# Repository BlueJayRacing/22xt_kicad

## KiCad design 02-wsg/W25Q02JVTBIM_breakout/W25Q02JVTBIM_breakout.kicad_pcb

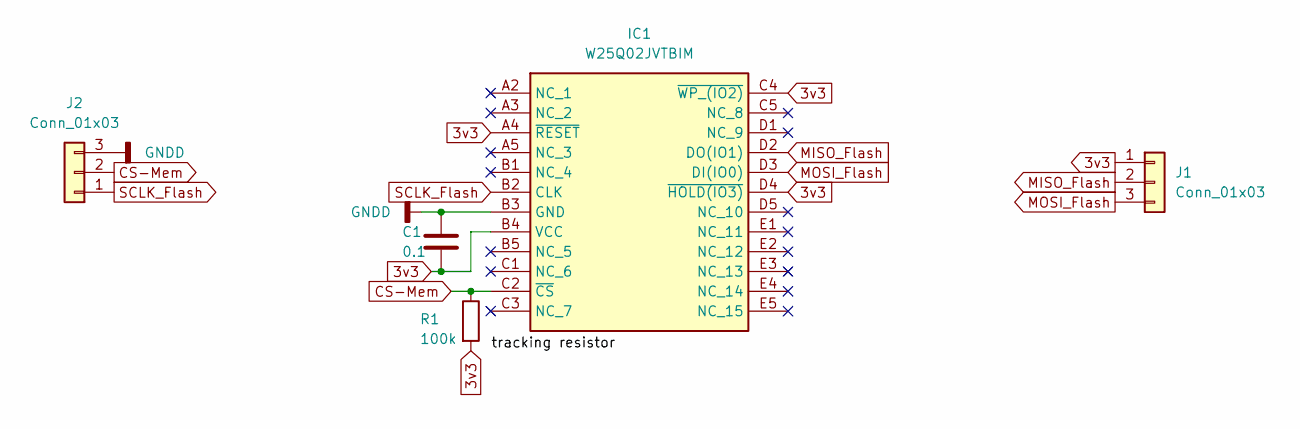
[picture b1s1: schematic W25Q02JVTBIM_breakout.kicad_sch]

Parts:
C1: 0.1; C_0402_1005Metric
IC1: W25Q02JVTBIM; BGA24C100P5X5_600X800X120; Mouser Part Number 454-W25Q02JVTBIM
J1, J2: Conn_01x03; PinHeader_1x03_P2.54mm_Vertical
R1: 100k; C_0402_1005Metric

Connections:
3v3: C1.2, IC1.A4 (~RESET), IC1.B4 (VCC), IC1.C4 (~WP_(IO2)), IC1.D4 (~HOLD(IO3)), J1.1, R1.2
CS-Mem: IC1.C2 (~CS), J2.2, R1.1
GNDD: C1.1, IC1.B3 (GND), J2.3
MISO_Flash: IC1.D2 (DO(IO1)), J1.2
MOSI_Flash: IC1.D3 (DI(IO0)), J1.3
SCLK_Flash: IC1.B2 (CLK), J2.1

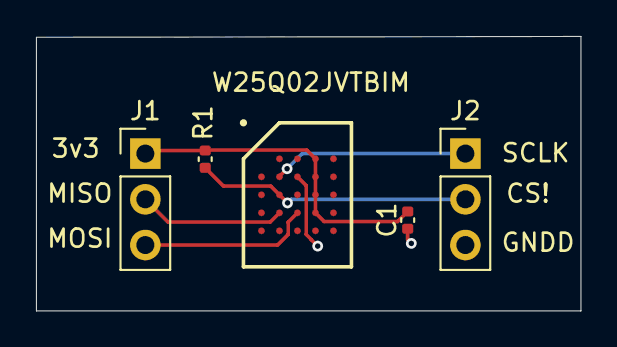
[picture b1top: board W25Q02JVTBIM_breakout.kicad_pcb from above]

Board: 2 copper layers, 30.3 x 15.2 mm, 5 parts (0 on the bottom side), 6 nets.

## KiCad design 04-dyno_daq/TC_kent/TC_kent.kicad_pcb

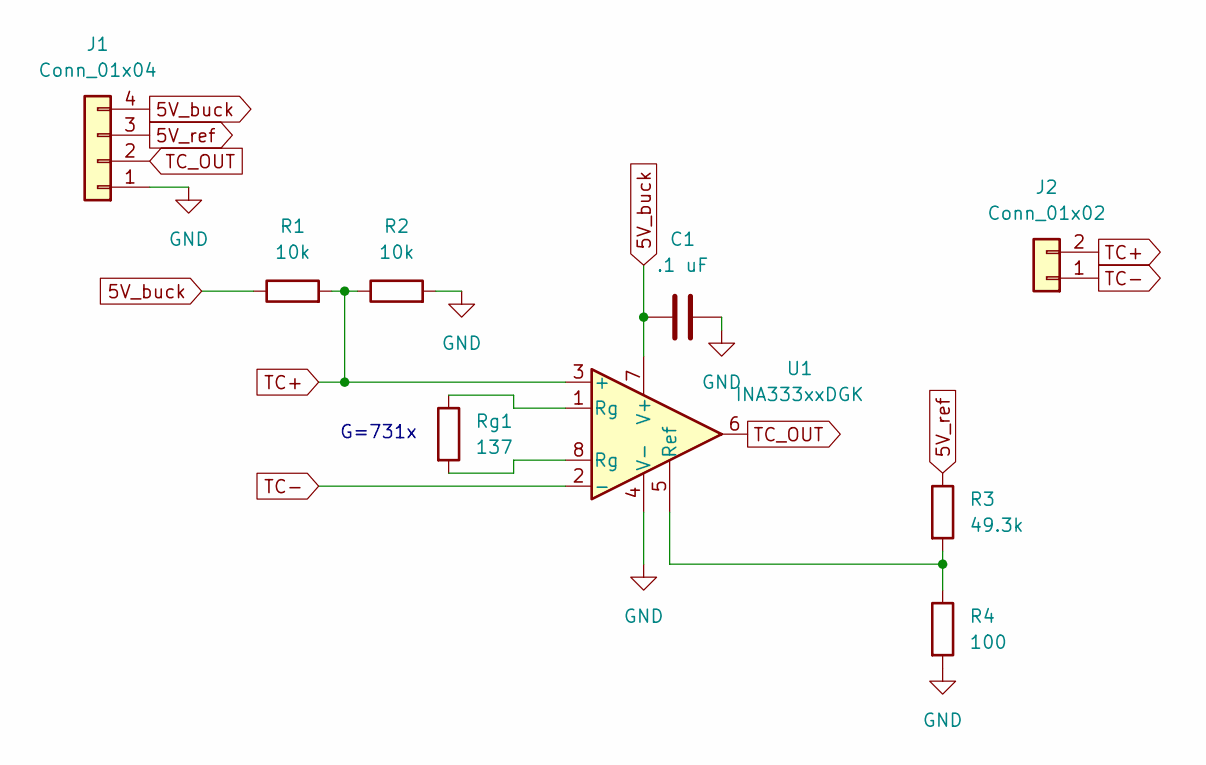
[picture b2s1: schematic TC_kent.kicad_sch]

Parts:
C1: .1 uF; C_0402_1005Metric
J1: Conn_01x04; JST_PH_B4B-PH-SM4-TB_1x04-1MP_P2.00mm_Vertical
J2: Conn_01x02; JST_PH_B2B-PH-SM4-TB_1x02-1MP_P2.00mm_Vertical
R1, R2: 10k; R_0402_1005Metric
R3: 49.3k; R_0402_1005Metric
R4: 100; R_0402_1005Metric
Rg1: 137; R_0402_1005Metric
U1: INA333xxDGK; VSSOP-8_3x3mm_P0.65mm

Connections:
5V_buck: C1.1, J1.4, R1.1, U1.7 (V+)
5V_ref: J1.3, R3.1
GND: C1.2, J1.1, R2.2, R4.2, U1.4 (V-)
unnamed: Rg1.1, U1.1 (Rg)
unnamed: Rg1.2, U1.8 (Rg)
unnamed: R3.2, R4.1, U1.5 (Ref)
TC+: J2.2, R1.2, R2.1, U1.3 (+)
TC-: J2.1, U1.2 (-)
TC_OUT: J1.2, U1.6

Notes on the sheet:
G=731x

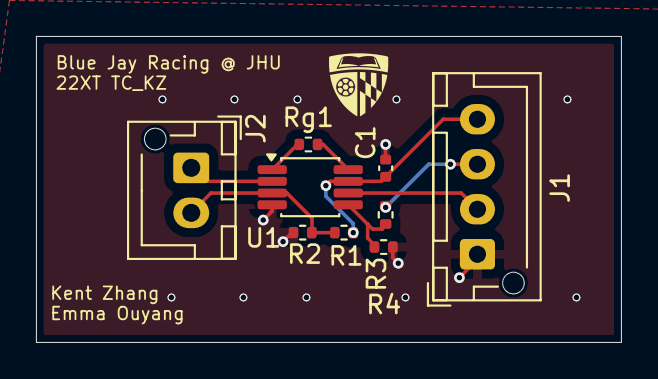
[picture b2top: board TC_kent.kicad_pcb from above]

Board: 2 copper layers, 32.5 x 17.0 mm, 9 parts (0 on the bottom side), 9 nets.

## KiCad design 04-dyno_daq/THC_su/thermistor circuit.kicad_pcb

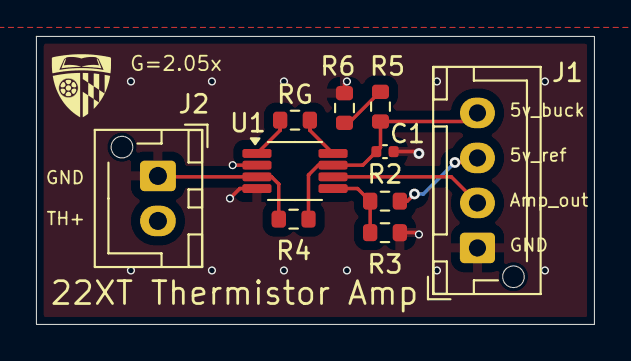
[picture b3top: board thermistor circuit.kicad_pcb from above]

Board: 2 copper layers, 31.0 x 16.0 mm, 10 parts (0 on the bottom side), 9 nets.

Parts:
C1: 0.1uf; C_0402_1005Metric
J1: Conn_01x04; JST_XH_B4B-XH-AM_1x04_P2.50mm_Vertical
J2: Conn_01x02; JST_XH_B2B-XH-AM_1x02_P2.50mm_Vertical
R2: 7.68k; R_0603_1608Metric
R3: 2.32k; R_0603_1608Metric
R4: 2k; R_0603_1608Metric
R5: 2.49k; R_0603_1608Metric
R6: 4.02k; R_0603_1608Metric
RG: 95.3k; R_0603_1608Metric
U1: INA333xxDGK; VSSOP-8_3x3mm_P0.65mm

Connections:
5v_buck: C1.1, J1.4, R4.1, R5.1, U1.7 (V+)
5v_ref: J1.3, R2.1
GND: C1.2, J1.1, J2.1, R3.2, R6.2, U1.2 (-), U1.4 (V-)
unnamed: RG.1, U1.1 (Rg)
unnamed: RG.2, U1.8 (Rg)
unnamed: R5.2, R6.1
unnamed: R2.2, R3.1, U1.5 (Ref)
TH+: J2.2, R4.2, U1.3 (+)
TH_AMP_OUT: J1.2, U1.6

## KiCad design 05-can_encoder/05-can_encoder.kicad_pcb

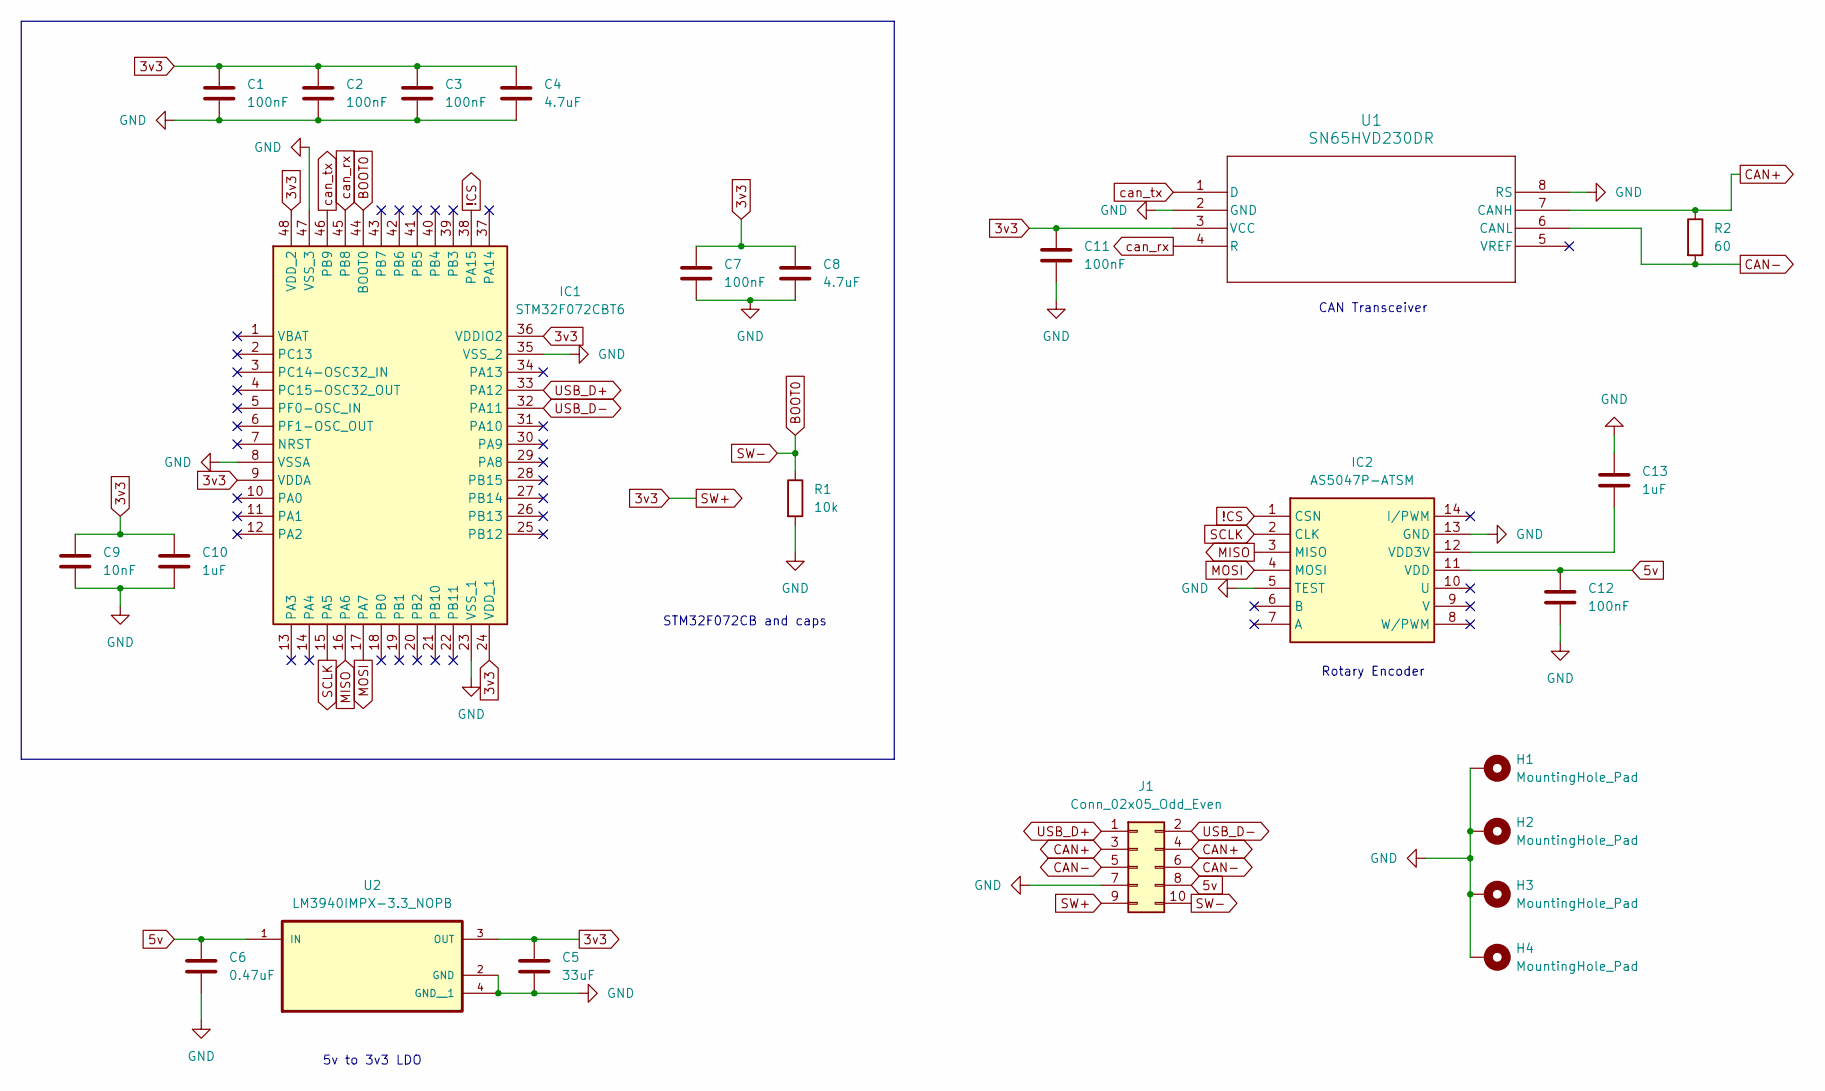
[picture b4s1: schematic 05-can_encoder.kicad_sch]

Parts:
C1, C2, C3, C7, C11, C12: 100nF; C_0603_1608Metric
C4, C8: 4.7uF; C_0603_1608Metric
C5: 33uF; C_0603_1608Metric
C6: 0.47uF; C_0603_1608Metric
C9: 10nF; C_0603_1608Metric
C10, C13: 1uF; C_0603_1608Metric
H1, H2, H3, H4: MountingHole_Pad; MountingHole_2.2mm_M2_DIN965_Pad
IC1: STM32F072CBT6; Mouser Part Number 511-STM32F072CBT6
IC2: AS5047P-ATSM; Mouser Part Number 985-AS5047P-ATSM
J1: Conn_02x05_Odd_Even; PinHeader_2x05_P2.54mm_Vertical
R1: 10k; R_0603_1608Metric
R2: 60; R_0603_1608Metric
U1: SN65HVD230DR
U2: LM3940IMPX-3.3_NOPB; LM3940IMPX

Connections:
3v3: C1.1, C2.1, C3.1, C4.1, C5.1, C7.1, C8.1, C9.1, C10.1, C11.1, IC1.9 (VDDA), IC1.24 (VDD_1), IC1.36 (VDDIO2), IC1.48 (VDD_2), J1.9, U1.3 (VCC), U2.3 (OUT)
5v: C6.1, C12.1, IC2.11 (VDD), J1.8, U2.1 (IN)
!CS: IC1.38 (PA15), IC2.1 (CSN)
BOOT0: IC1.44 (BOOT0), J1.10, R1.1
CAN+: J1.3, J1.4, R2.1, U1.7 (CANH)
CAN-: J1.5, J1.6, R2.2, U1.6 (CANL)
GND: C1.2, C2.2, C3.2, C4.2, C5.2, C6.2, C7.2, C8.2, C9.2, C10.2, C11.2, C12.2, C13.2, H1.1, H2.1, H3.1, H4.1, IC1.8 (VSSA), IC1.23 (VSS_1), IC1.35 (VSS_2), IC1.47 (VSS_3), IC2.5 (TEST), IC2.13 (GND), J1.7, R1.2, U1.2 (GND), U1.8 (RS), U2.2 (GND), U2.4 (GND__1)
MISO: IC1.16 (PA6), IC2.3 (MISO)
MOSI: IC1.17 (PA7), IC2.4 (MOSI)
unnamed: C13.1, IC2.12 (VDD3V)
SCLK: IC1.15 (PA5), IC2.2 (CLK)
USB_D+: IC1.33 (PA12), J1.1
USB_D-: IC1.32 (PA11), J1.2
can_rx: IC1.45 (PB8), U1.4 (R)
can_tx: IC1.46 (PB9), U1.1 (D)

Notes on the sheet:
5v to 3v3 LDO
Rotary Encoder
STM32F072CB and caps
CAN Transceiver

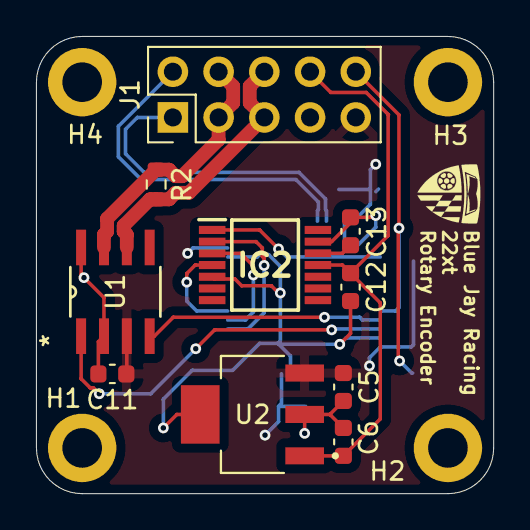
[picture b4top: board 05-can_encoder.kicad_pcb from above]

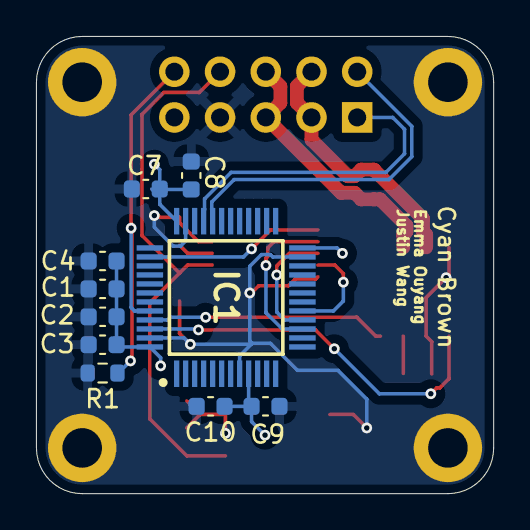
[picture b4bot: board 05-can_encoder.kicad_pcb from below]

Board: 2 copper layers, 25.4 x 25.4 mm, 24 parts (10 on the bottom side), 15 nets.

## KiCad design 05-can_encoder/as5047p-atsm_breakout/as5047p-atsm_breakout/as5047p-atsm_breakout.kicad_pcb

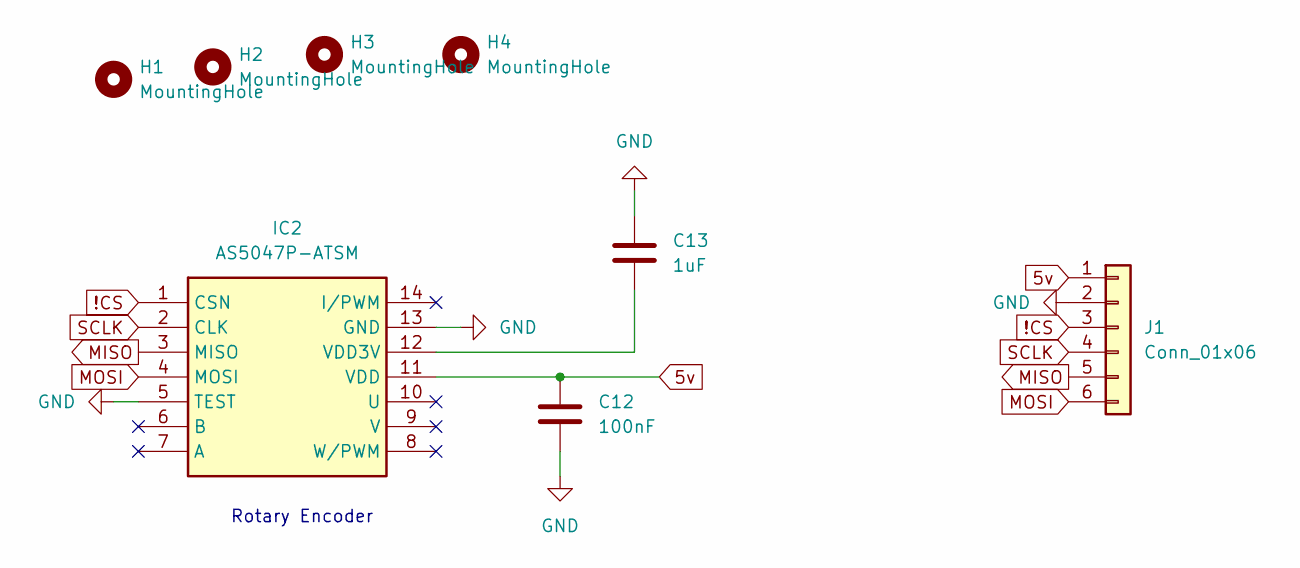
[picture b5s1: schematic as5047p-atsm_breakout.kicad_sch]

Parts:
C12: 100nF; C_0603_1608Metric
C13: 1uF; C_0603_1608Metric
H1, H2, H3, H4: MountingHole; MountingHole_2.2mm_M2
IC2: AS5047P-ATSM; Mouser Part Number 985-AS5047P-ATSM
J1: Conn_01x06; PinHeader_1x06_P2.54mm_Vertical

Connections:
5v: C12.1, IC2.11 (VDD), J1.1
!CS: IC2.1 (CSN), J1.3
GND: C12.2, C13.2, IC2.5 (TEST), IC2.13 (GND), J1.2
MISO: IC2.3 (MISO), J1.5
MOSI: IC2.4 (MOSI), J1.6
unnamed: C13.1, IC2.12 (VDD3V)
SCLK: IC2.2 (CLK), J1.4

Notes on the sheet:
Rotary Encoder

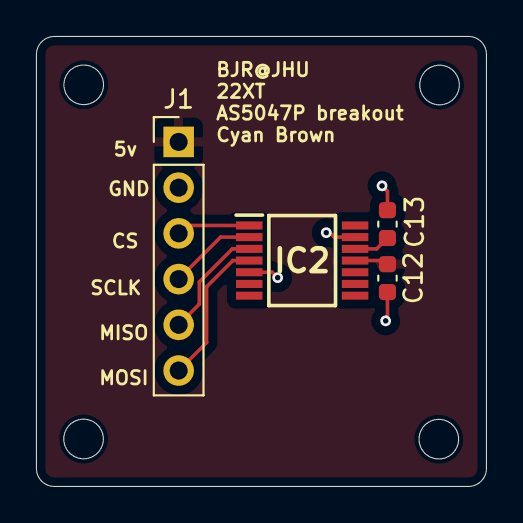
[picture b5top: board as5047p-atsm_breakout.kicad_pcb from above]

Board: 2 copper layers, 25.0 x 25.0 mm, 8 parts (0 on the bottom side), 7 nets.

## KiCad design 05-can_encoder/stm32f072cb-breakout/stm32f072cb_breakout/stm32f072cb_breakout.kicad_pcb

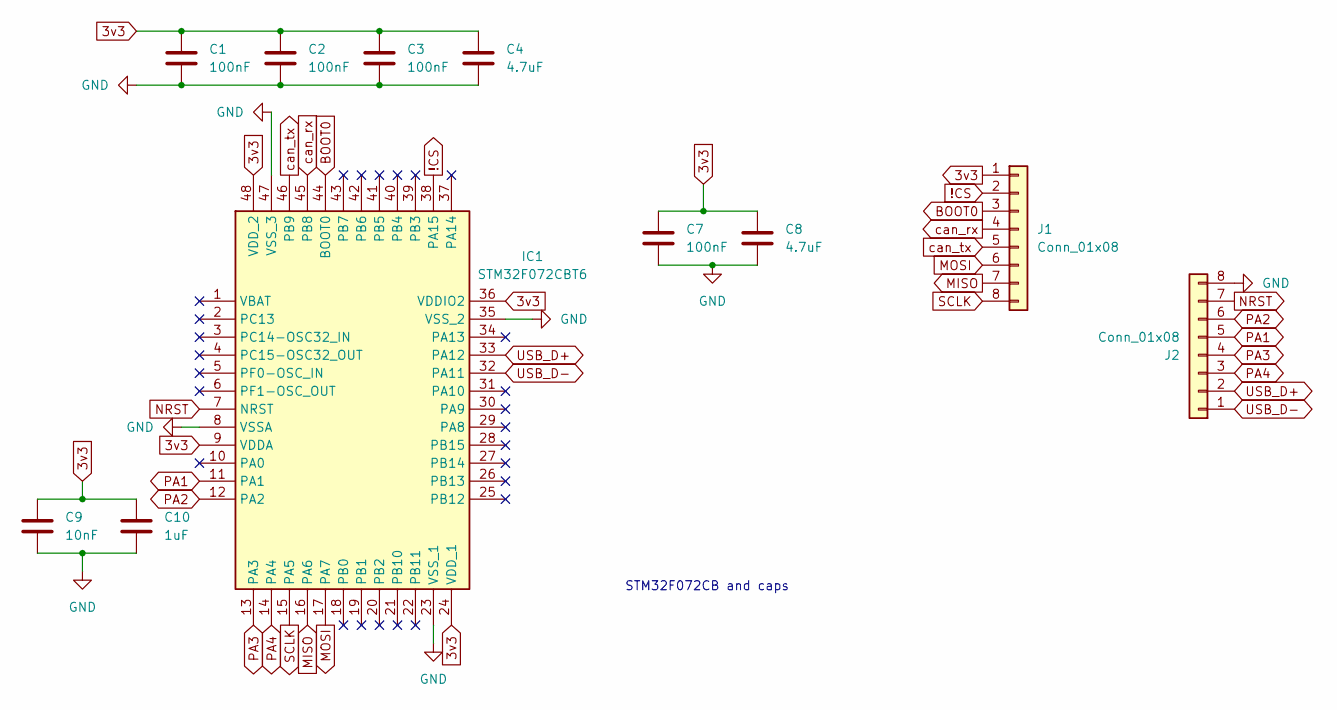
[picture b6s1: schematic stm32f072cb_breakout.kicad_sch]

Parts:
C1, C2, C3, C7: 100nF; C_0603_1608Metric
C4, C8: 4.7uF; C_0603_1608Metric
C9: 10nF; C_0603_1608Metric
C10: 1uF; C_0603_1608Metric
IC1: STM32F072CBT6; Mouser Part Number 511-STM32F072CBT6
J1, J2: Conn_01x08; PinHeader_1x08_P2.54mm_Vertical

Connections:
3v3: C1.1, C2.1, C3.1, C4.1, C7.1, C8.1, C9.1, C10.1, IC1.9 (VDDA), IC1.24 (VDD_1), IC1.36 (VDDIO2), IC1.48 (VDD_2), J1.1
!CS: IC1.38 (PA15), J1.2
BOOT0: IC1.44 (BOOT0), J1.3
GND: C1.2, C2.2, C3.2, C4.2, C7.2, C8.2, C9.2, C10.2, IC1.8 (VSSA), IC1.23 (VSS_1), IC1.35 (VSS_2), IC1.47 (VSS_3), J2.8
MISO: IC1.16 (PA6), J1.7
MOSI: IC1.17 (PA7), J1.6
NRST: IC1.7 (NRST), J2.7
PA1: IC1.11 (PA1), J2.5
PA2: IC1.12 (PA2), J2.6
PA3: IC1.13 (PA3), J2.4
PA4: IC1.14 (PA4), J2.3
SCLK: IC1.15 (PA5), J1.8
USB_D+: IC1.33 (PA12), J2.2
USB_D-: IC1.32 (PA11), J2.1
can_rx: IC1.45 (PB8), J1.4
can_tx: IC1.46 (PB9), J1.5

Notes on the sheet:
STM32F072CB and caps

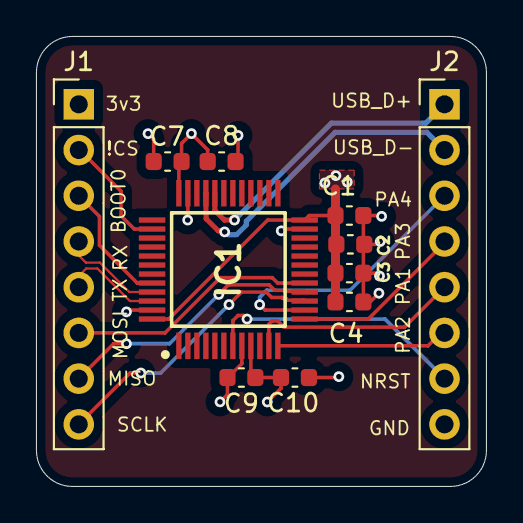
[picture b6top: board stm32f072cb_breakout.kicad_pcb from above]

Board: 4 copper layers, 25.0 x 25.0 mm, 11 parts (0 on the bottom side), 16 nets.
